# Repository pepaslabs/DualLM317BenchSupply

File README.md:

DualLM317BenchSupply
====================

A simple adjustable voltage, current limited bench power supply using two LM317 regulators, designed in KiCAD.

Features:

* Voltage is variable, using a 10-turn pot.
* Current is limited in 6 steps (13mA, 25mA, 63mA, 125mA, 250mA, 500mA).
* A current-limit bypass switch allows for more than 500mA.  Be careful not to exceed 1.5A.  This is the "trust me, I know what I'm doing" switch.
* Footprints included for both 2.1x5.5mm and 2.5x5.5mm DC barrel jacks (the two sizes you are most likely to have on hand).
* Modifications possible by populating the board with alternate parts

Latest Schematic:

[View schematic as PDF](https://github.com/pepaslabs/DualLM317BenchSupply/raw/master/DualLM317BenchSupply_schematic.pdf).

## License

Parts which I have created are released under the [MIT License](http://opensource.org/licenses/MIT).  Parts which I have modified are subject to their original license.

## Board Revision v2

Revision 2 of the boards are being beta tested amongst some friends.  I'll probably put it up on tindie.com soon!

* KiCAD files: https://github.com/pepaslabs/DualLM317BenchSupply/archive/v2.0.zip
* Bill Of Materials: https://docs.google.com/spreadsheets/d/1UEHeVoLBXWML7s4iypZqZUHYBSBsEXaSeRBIaHcoUhg/edit?usp=sharing
* Assembly Instructions: https://www.evernote.com/shard/s301/sh/98922a1c-4789-4eff-8265-b3d52353a5f1/38aa0f58f0495949719a24fac0aefa83

## Board Revision v1

A run of five v1 boards was ordered, but they suffered from a manufacturing defect which shorted a pad to ground.  Thus, this revision was never publicly for sale.

* KiCAD files: https://github.com/pepaslabs/DualLM317BenchSupply/archive/v1.0.zip
* Bill Of Materials: https://docs.google.com/spreadsheets/d/1L0ausNb0WpCJjKkbzb2hiCHUUvhVTbAR-jT5hPuG_W0/edit?usp=sharing

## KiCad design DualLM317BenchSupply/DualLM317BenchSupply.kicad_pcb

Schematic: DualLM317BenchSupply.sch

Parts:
C101: 1000uF
C102, C105, C107, C110: 1uF
C103, C108, C109: 0.1uF
C104, C106: 10uF
CON101, CON102: BARREL_JACK
D101, D102, D104, D105: 1N4148
D103: LED
DS101: VOLTMETER
DS102: AMMETER_V
H101, H102, H103, H104: HOLE
P101: Vout+
P102: Vout-
R101: 150
R102: 330
RV101: 4.7k
RV102: 10
SW101, SW102, SW103: SPDT
U101: 7812
U102, U103: LM317
U104: 7805

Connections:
5V: C104.1, C108.1, C109.1, D103.1 (A), DS101.2, DS102.3, U104.3 (OUT)
12V: C110.1, U101.3 (OUT), U104.1 (IN)
/current_limit_r/R_LIM+: D101.1 (A), D102.2 (K), U102.2 (OUT); also elsewhere on the board
/current_limit_r/R_LIM-: C105.1, D102.1 (A), D104.2 (K), SW102.1, U102.1 (ADJ), U103.3 (IN); also elsewhere on the board
GND: C101.2, C102.2, C103.2, C104.2, C105.2, C106.2, C107.2, C108.2, C109.2, C110.2, CON101.2, CON101.3, CON102.2, CON102.3, DS101.3, DS102.2, DS102.4, R101.2, RV101.1, RV102.2, RV102.3, U101.2 (GND), U104.2 (GND)
unnamed: C107.1, D104.1 (A), D105.2 (K), DS101.1, R102.1, SW103.2, U103.2 (OUT)
unnamed: C106.1, D105.1 (A), R102.2, RV101.2, RV101.3, U103.1 (ADJ)
unnamed: P101.1, SW103.1
unnamed: DS102.1, P102.1, RV102.1
unnamed: D103.2 (K), R101.1
unnamed: CON101.1, CON102.1, SW101.2
unnamed: C101.1, C102.1, C103.1, D101.2 (K), SW101.1, SW102.2, U101.1 (IN), U102.3 (IN)

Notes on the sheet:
Current Limit Bypass
Vout (1.25V - 20.2V DC)
Vin (24V DC)
Voltage Limiting
Current Limiting
Status LED
Power On / Off
Output Enable / Disable
330 & 4.7k = 19V max
5V Supply
2.1 x 5.5mm
2.5 x 5.5mm

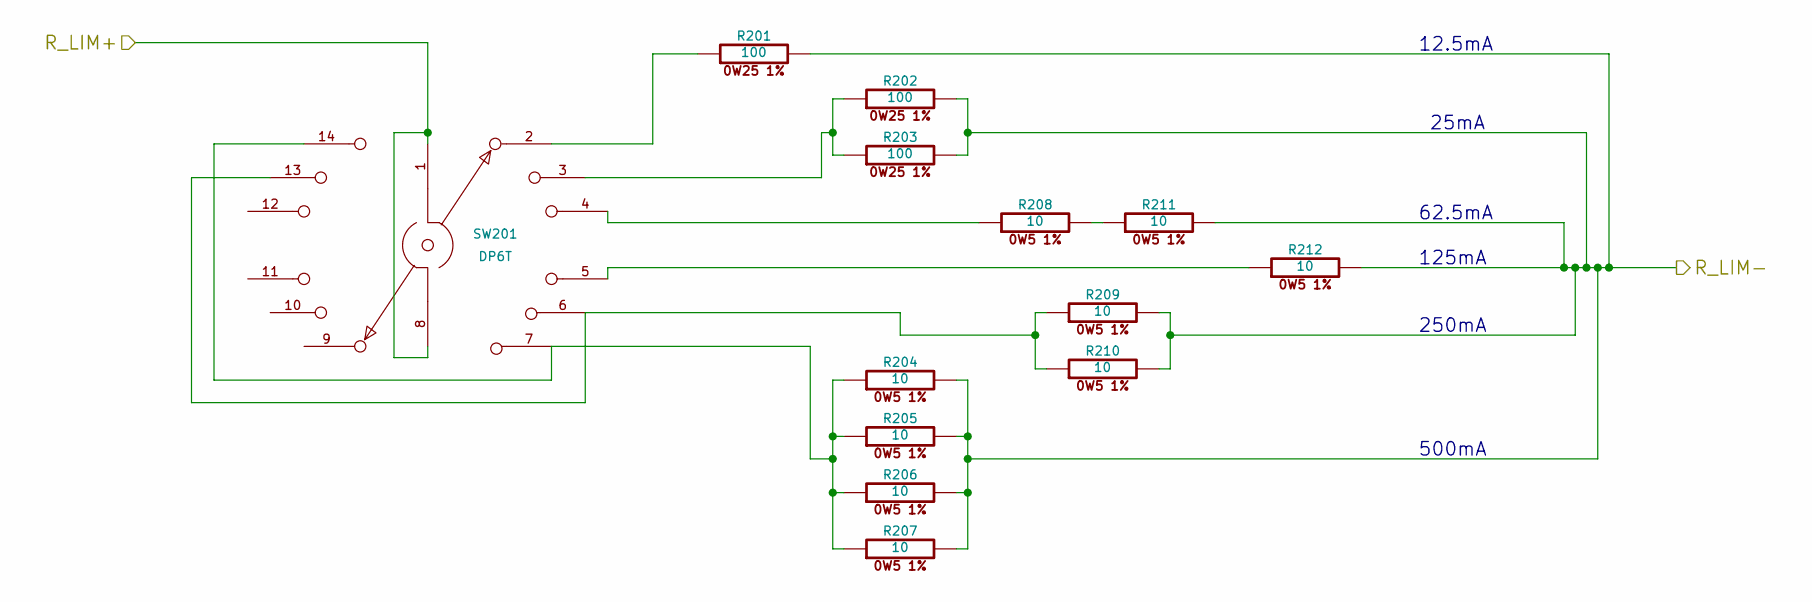
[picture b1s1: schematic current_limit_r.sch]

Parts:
R201, R202, R203: 100
R204, R205, R206, R207, R208, R209, R210, R211, R212: 10
SW201: DP6T

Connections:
/current_limit_r/R_LIM+: SW201.1, SW201.8; also elsewhere on the board
/current_limit_r/R_LIM-: R201.2, R202.2, R203.2, R204.2, R205.2, R206.2, R207.2, R209.2, R210.2, R211.2, R212.2; also elsewhere on the board
unnamed: R209.1, R210.1, SW201.6, SW201.13
unnamed: R204.1, R205.1, R206.1, R207.1, SW201.7, SW201.14
unnamed: R208.2, R211.1
unnamed: R212.1, SW201.5
unnamed: R208.1, SW201.4
unnamed: R201.1, SW201.2
unnamed: R202.1, R203.1, SW201.3

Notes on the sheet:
12.5mA
25mA
62.5mA
125mA
250mA
500mA

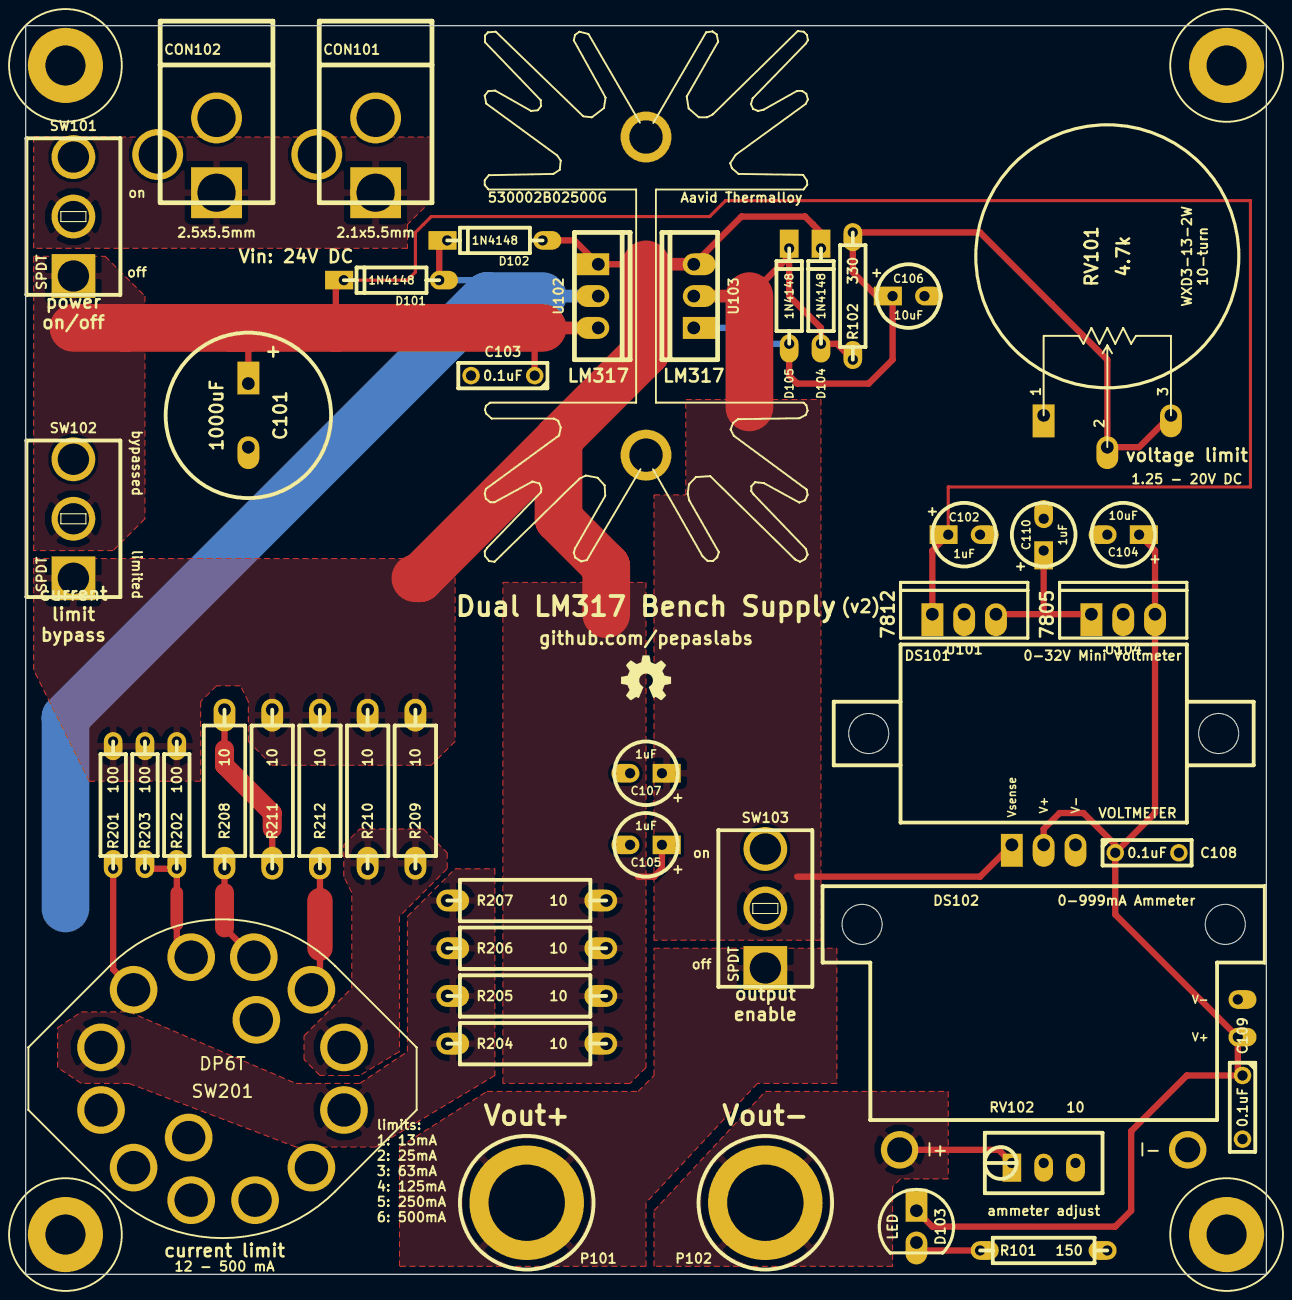
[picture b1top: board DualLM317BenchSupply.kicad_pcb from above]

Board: 2 copper layers, 99.1 x 99.7 mm, 50 parts (0 on the bottom side), 19 nets.

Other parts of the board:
H***: 530002B02500G

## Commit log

2014-03-01 Initial project creation
2014-03-01 basic schematic laid out.
2014-03-16 updating design to use 6 position switch to select current limiting resistor.
2014-03-16 adding input / output switches, revising schematic parts.
2014-03-16 adding voltmeter and ammeter
2014-03-16 annotating parts. adding printout of schematic.
2014-03-16 adding voltmeter / ammeter
2014-03-16 updating printout
2014-03-17 revising protection diodes
2014-03-17 adding connectors and heatsinks libs
2014-03-17 updating switch
2014-03-17 updating parts
2014-03-17 updating switches, capacitors, and LEDs
2014-03-18 reconfiguring protection diodes
2014-03-18 moving status LED to 5V rail. starting initial layout.
2014-03-18 updating schematic
2014-03-20 reconfiguring ammeter to be low-side, not high-side.
2014-03-21 switching to voltmeter based on real ground, not Vout- (introduced too much error into the ammeter)
2014-03-21 updating schematic printout.
2014-03-22 specifying 1% for current limiting resistors (lower temp co). also, moving 10R resistors to 1/2 watt.
2014-03-22 working on board layout
2014-03-23 updating resistor footprint filters
2014-03-23 working on layout of current limit selector switch resistors.
2014-03-23 adding second dc jack
2014-03-23 adding mounting holes to schematic
2014-03-23 dc jacks
2014-03-23 working on input layout
2014-03-23 working on current limit switch layout
2014-03-23 working on layout
2014-03-23 pulling in updated parts
2014-03-23 pulling in diodes lib
2014-03-23 updating layout
2014-03-23 adding voltmeter and potentiometer to layout
2014-03-24 adding ammeter footprint
2014-03-28 correcting pads for ammeter and running traces to it
2014-03-28 adding caps for meters
2014-03-28 tweaked board labels and created v1 gerbers
2014-03-28 adding back silkscreen
2014-04-01 updating pngs
2014-04-19 thinning cap trace for solderability
2014-04-19 thinning traces for solderability
2014-04-19 thinning out traces for solderability
2014-04-19 bumping board version. more trace thinning.
2014-04-19 updating gerbers
2014-04-19 updating project file
2014-04-20 updating pdf printout
2014-04-20 adding 7812 before the 7805 to distribute the thermal load (a 7812 is cheaper than a heatsink :).
2014-04-21 using fills instead of traces for high current areas
2014-04-21 more tweaks to fills
2014-04-21 zipping up gerbers for v2
2014-04-21 updating barrell jack footprints
2017-04-22 adding board shots
2017-04-22 updating readme
